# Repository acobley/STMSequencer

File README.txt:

Production board was :
StmPulse-V1-G49804

*Note* the design has a fault.  R2 and R5 are attached to 5V but should be attached to +5V

I added an airwire to link them on my build.

*NOTE*  the trigger output on board StmPulse-V1-G49804 was only 3.3V whihc is not enough to trigger some modules.

*StmPulse-V2-InProgress.sch*
This fixes the above faults, it connects R2 and R5 to +5V and adds output transistors on the gates to give 5V.

StmPulse-V2-InProgress has *NOT* been built or tested.

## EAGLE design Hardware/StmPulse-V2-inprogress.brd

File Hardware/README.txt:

Production board was :
StmPulse-V1-G49804

*Note* the design has a fault.  R2 and R5 are attached to 5V but should be attached to +5V

I added an airwire to link them on my build.

*NOTE*  the trigger output on board StmPulse-V1-G49804 was only 3.3V whihc is not enough to trigger some modules.

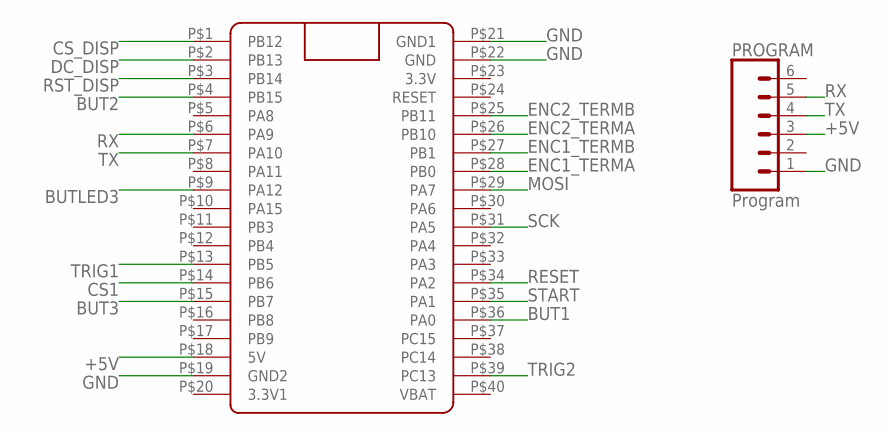
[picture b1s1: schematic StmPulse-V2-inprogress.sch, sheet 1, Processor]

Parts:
PROGRAM: Program; 1X06
U$1: Blue Pill; BLUE_PILL

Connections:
+5V: PROGRAM.3, U$1.P$18 (5V); also elsewhere on the board
BUT1: U$1.P$36 (PA0); also elsewhere on the board
BUT2: U$1.P$4 (PB15); also elsewhere on the board
BUT3: U$1.P$15 (PB7); also elsewhere on the board
BUTLED3: U$1.P$9 (PA12); also elsewhere on the board
CS1: U$1.P$14 (PB6); also elsewhere on the board
CS_DISP: U$1.P$1 (PB12); also elsewhere on the board
DC_DISP: U$1.P$2 (PB13); also elsewhere on the board
ENC1_TERMA: U$1.P$28 (PB0); also elsewhere on the board
ENC1_TERMB: U$1.P$27 (PB1); also elsewhere on the board
ENC2_TERMA: U$1.P$26 (PB10); also elsewhere on the board
ENC2_TERMB: U$1.P$25 (PB11); also elsewhere on the board
GND: PROGRAM.1, U$1.P$19 (GND2), U$1.P$21 (GND1), U$1.P$22 (GND); also elsewhere on the board
MOSI: U$1.P$29 (PA7); also elsewhere on the board
RESET: U$1.P$34 (PA2); also elsewhere on the board
RST_DISP: U$1.P$3 (PB14); also elsewhere on the board
RX: PROGRAM.5, U$1.P$6 (PA9)
SCK: U$1.P$31 (PA5); also elsewhere on the board
START: U$1.P$35 (PA1); also elsewhere on the board
TRIG1: U$1.P$13 (PB5); also elsewhere on the board
TRIG2: U$1.P$39 (PC13); also elsewhere on the board
TX: PROGRAM.4, U$1.P$7 (PA10)

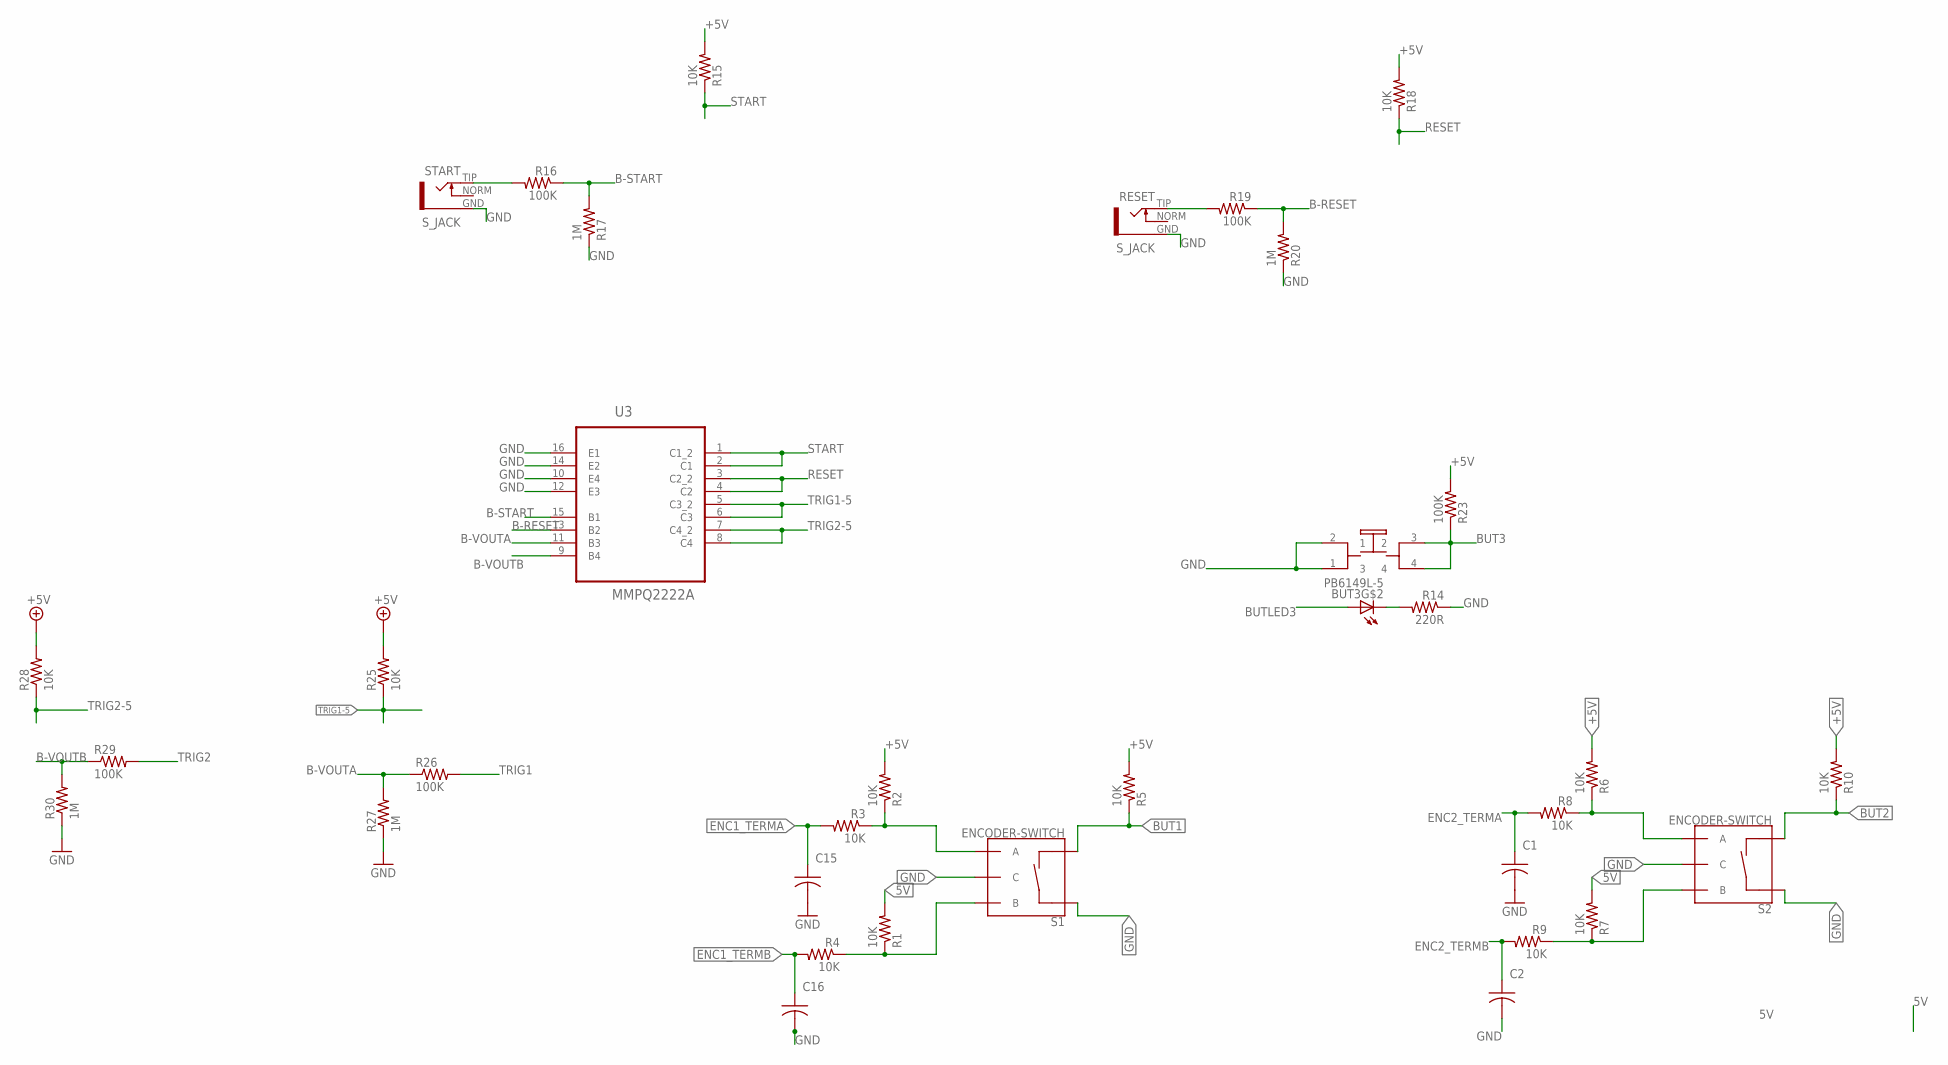
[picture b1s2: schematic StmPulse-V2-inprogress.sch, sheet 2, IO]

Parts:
BUT3: PB6149L-5; PB6149L
C1, C2, C15, C16: 10nF; C0805
R1, R2, R3, R4, R5, R6, R7, R8, R9, R10, R15, R18, R25, R28: 10K; R0805
R14: 220R; R0805
R16, R19, R23, R26, R29: 100K; R0805
R17, R20, R27, R30: 1M; R0805
RESET: S_JACK
S1, S2: ENCODER-SWITCH; ROTARY_ENC_PLAIN
START: S_JACK
U3: MMPQ2222A; SOIC127P600X175-16N

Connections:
5V: R1.2, R7.2
+5V: R2.2, R5.2, R6.2, R10.2, R15.2, R18.2, R23.2, R25.2, R28.2; also elsewhere on the board
B-RESET: R19.1, R20.2, U3.13 (B2)
B-START: R16.1, R17.2, U3.15 (B1)
B-VOUTA: R26.1, R27.2, U3.11 (B3)
B-VOUTB: R29.1, R30.2, U3.9 (B4)
BUT1: R5.1, S1.SW-; also elsewhere on the board
BUT2: R10.1, S2.SW-; also elsewhere on the board
BUT3: BUT3.3 (2), BUT3.4, R23.1; also elsewhere on the board
BUTLED3: BUT3.A; also elsewhere on the board
ENC1_TERMA: C15.1, R3.2; also elsewhere on the board
ENC1_TERMB: C16.1, R4.2; also elsewhere on the board
ENC2_TERMA: C1.1, R8.2; also elsewhere on the board
ENC2_TERMB: C2.1, R9.2; also elsewhere on the board
GND: BUT3.1 (3), BUT3.2 (1), C1.2, C2.2, C15.2, C16.2, R14.1, R17.1, R20.1, R27.1, R30.1, RESET.GND, S1.C, S1.SW+, S2.C, S2.SW+, START.GND, U3.10 (E4), U3.12 (E3), U3.14 (E2), U3.16 (E1); also elsewhere on the board
unnamed: R6.1, R8.1, S2.A
unnamed: R7.1, R9.1, S2.B
unnamed: R2.1, R3.1, S1.A
unnamed: R1.1, R4.1, S1.B
unnamed: BUT3.K (C), R14.2
unnamed: R19.2, RESET.TIP
unnamed: R16.2, START.TIP
RESET: R18.1, U3.3 (C2_2), U3.4 (C2); also elsewhere on the board
START: R15.1, U3.1 (C1_2), U3.2 (C1); also elsewhere on the board
TRIG1: R26.2; also elsewhere on the board
TRIG1-5: R25.1, U3.5 (C3_2), U3.6 (C3); also elsewhere on the board
TRIG2: R29.2; also elsewhere on the board
TRIG2-5: R28.1, U3.7 (C4_2), U3.8 (C4); also elsewhere on the board

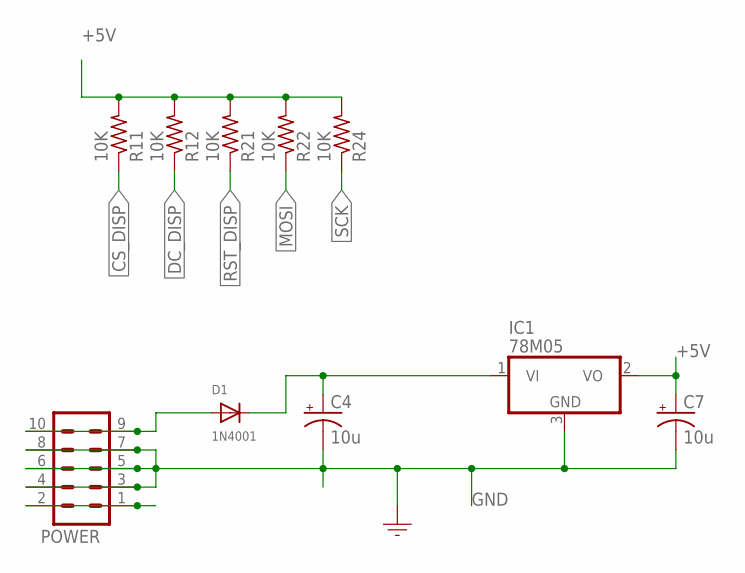
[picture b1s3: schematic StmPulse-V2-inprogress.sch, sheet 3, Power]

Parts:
C4, C7: 10u; 153CLV-0505
D1: 1N4001; SMADIODE
IC1: 78M05; TO252
POWER: CONN_05X2SHD_SMD; 2X5-SHROUDED_SMD
R11, R12, R21, R22, R24: 10K; R0805

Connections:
+5V: C7.+, IC1.2 (VO), R11.2, R12.2, R21.2, R22.2, R24.2; also elsewhere on the board
+12V: C4.+, D1.C, IC1.1 (VI)
CS_DISP: R11.1; also elsewhere on the board
DC_DISP: R12.1; also elsewhere on the board
GND: C4.-, C7.-, IC1.3 (GND), POWER.3, POWER.4, POWER.5, POWER.6, POWER.7, POWER.8; also elsewhere on the board
MOSI: R22.1; also elsewhere on the board
unnamed: D1.A, POWER.9, POWER.10
unnamed: POWER.1, POWER.2
RST_DISP: R21.1; also elsewhere on the board
SCK: R24.1; also elsewhere on the board

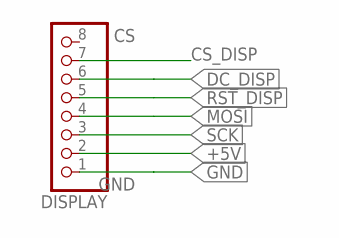
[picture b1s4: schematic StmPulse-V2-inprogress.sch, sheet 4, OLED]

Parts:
DISPLAY: MICROBUILDER_HEADER-1X8ROUND; MICROBUILDER_1X08_ROUND

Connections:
+5V: DISPLAY.2; also elsewhere on the board
CS_DISP: DISPLAY.7; also elsewhere on the board
DC_DISP: DISPLAY.6; also elsewhere on the board
GND: DISPLAY.1; also elsewhere on the board
MOSI: DISPLAY.4; also elsewhere on the board
RST_DISP: DISPLAY.5; also elsewhere on the board
SCK: DISPLAY.3; also elsewhere on the board

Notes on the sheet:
GND

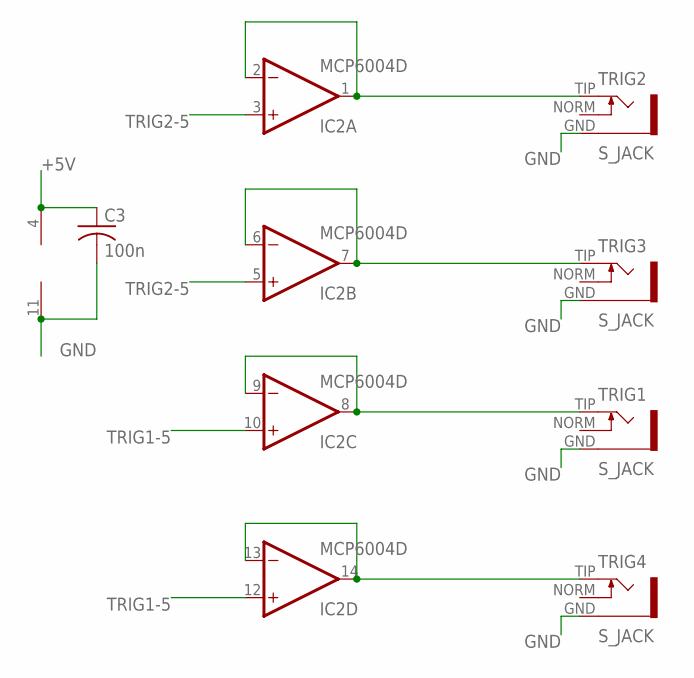
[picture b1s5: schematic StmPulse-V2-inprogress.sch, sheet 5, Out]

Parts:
C3: 100n; C0805K
IC2: MCP6004D; SO14
TRIG1, TRIG2, TRIG3, TRIG4: S_JACK

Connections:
+5V: C3.1, IC2.4 (V+); also elsewhere on the board
GND: C3.2, IC2.11 (V-), TRIG1.GND, TRIG2.GND, TRIG3.GND, TRIG4.GND; also elsewhere on the board
unnamed: IC2.1 (OUT), IC2.2 (-IN), TRIG2.TIP
unnamed: IC2.8 (OUT), IC2.9 (-IN), TRIG1.TIP
unnamed: IC2.6 (-IN), IC2.7 (OUT), TRIG3.TIP
unnamed: IC2.13 (-IN), IC2.14 (OUT), TRIG4.TIP
TRIG1-5: IC2.10 (+IN), IC2.12 (+IN); also elsewhere on the board
TRIG2-5: IC2.3 (+IN), IC2.5 (+IN); also elsewhere on the board

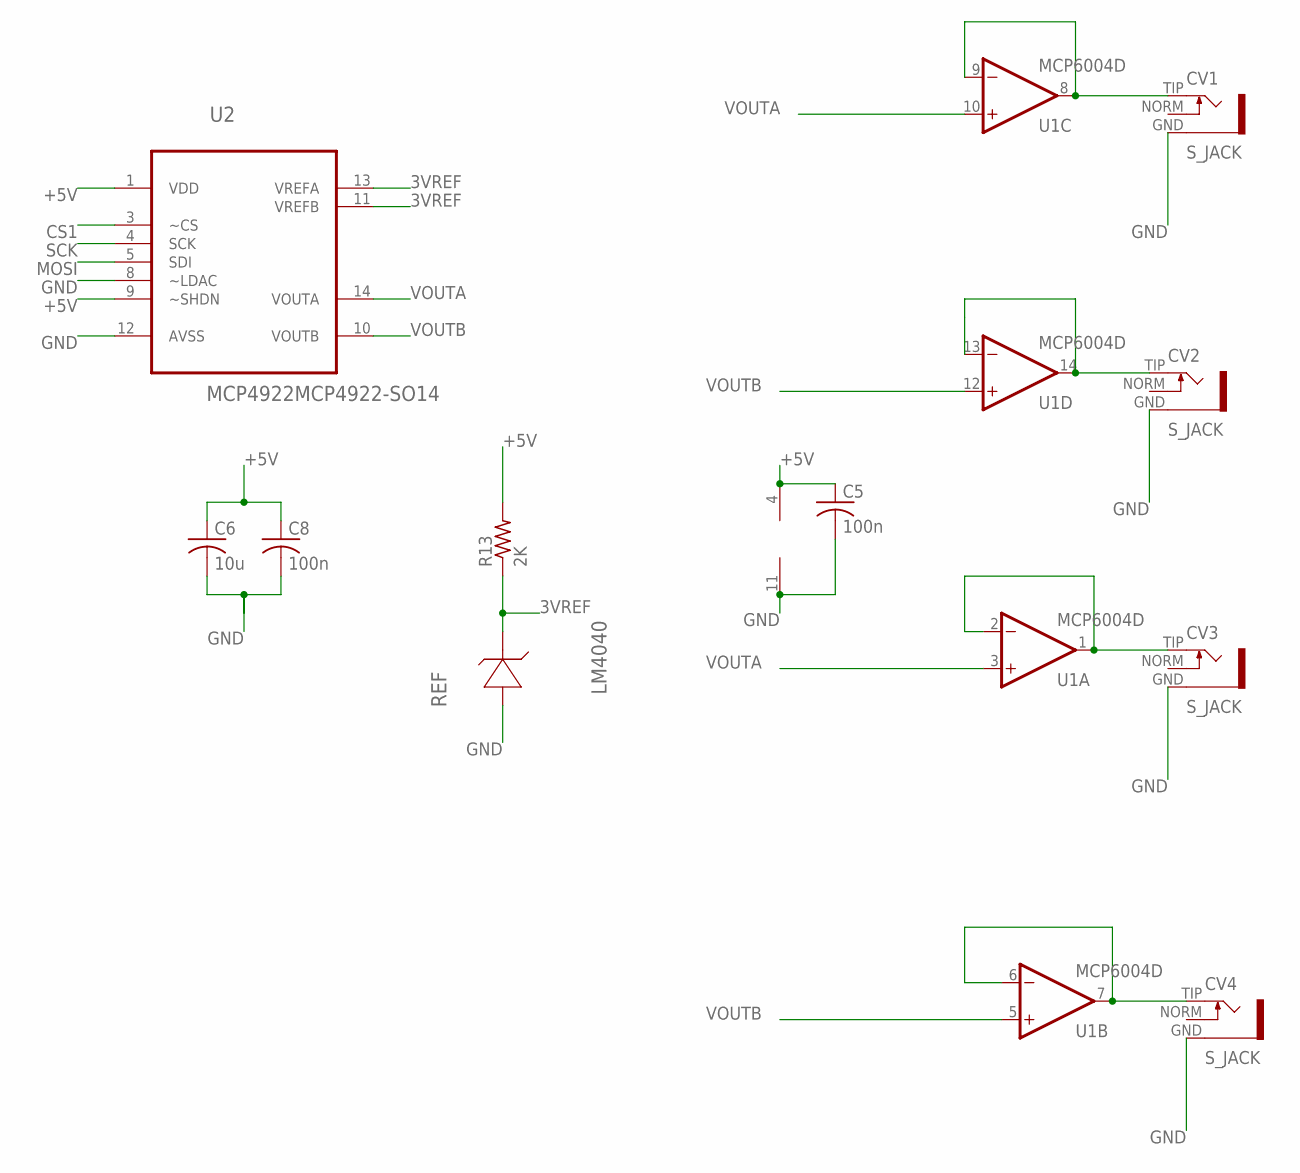
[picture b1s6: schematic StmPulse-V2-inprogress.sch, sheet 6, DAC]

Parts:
C5, C8: 100n; C0805K
C6: 10u; C0805K
CV1, CV2, CV3, CV4: S_JACK
R13: 2K; R0805
REF: LM4040; SOT95P237X112-3N; MPN LM4040A30IDBZT
U1: MCP6004D; SO14
U2: MCP4922MCP4922-SO14; SO14

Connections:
3VREF: R13.1, REF.1 (CATHODE), U2.11 (VREFB), U2.13 (VREFA)
+5V: C5.1, C6.1, C8.1, R13.2, U1.4 (V+), U2.1 (VDD), U2.9 (~SHDN); also elsewhere on the board
CS1: U2.3 (~CS); also elsewhere on the board
GND: C5.2, C6.2, C8.2, CV1.GND, CV2.GND, CV3.GND, CV4.GND, REF.2 (ANODE), U1.11 (V-), U2.8 (~LDAC), U2.12 (AVSS); also elsewhere on the board
MOSI: U2.5 (SDI); also elsewhere on the board
unnamed: CV3.TIP, U1.1 (OUT), U1.2 (-IN)
unnamed: CV4.TIP, U1.6 (-IN), U1.7 (OUT)
unnamed: CV1.TIP, U1.8 (OUT), U1.9 (-IN)
unnamed: CV2.TIP, U1.13 (-IN), U1.14 (OUT)
SCK: U2.4 (SCK); also elsewhere on the board
VOUTA: U1.3 (+IN), U1.10 (+IN), U2.14 (VOUTA)
VOUTB: U1.5 (+IN), U1.12 (+IN), U2.10 (VOUTB)

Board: 2 copper layers, 68 parts (14 on the bottom side), 50 nets, no tracks yet.

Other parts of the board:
U$2, U$3, U$4, U$5: MOUNTING_HOLE

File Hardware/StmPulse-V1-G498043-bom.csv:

"Library","Qty","Parts","Description","Value","Package","LABEL","LABLEL","MPN","OC_FARNELL","OC_NEWARK","PACKAGE","PROD_ID","RS-PART","SF_SKU","SUPPLIER",
"INSTRUO","1","T1_CLOCK","","2N3904","TRANSISTOR_SINGLE_N-TYPE","","T1_Start","","","","","","725-8616 ","","",
"BluePill","1","U$1","","Blue Pill","BLUE_PILL","","","","","","","","","","",
"GMSN-R2Project","1","U2-MCP4922","","MCP4922MCP4922-SO14","SO14","","","","","","","","402-910 ","","",
"INSTRUO","1","BUT3","","PB6149L-5","PB6149L","","","","","","","","","","",
"INSTRUO","10","CV1, CV2, CV3, CV4, RESET, START, TRIG1, TRIG2, TRIG3, TRIG4","","S_JACK","S_JACK","","","","","","","","","","",
"INSTRUO","1","T2_RESET","","TRANSISTOR_MMBT3904","TRANSISTOR_SINGLE_N-TYPE","T2_Reset","","","","","","","725-8616 ","","",
"rcl","3","C3, C5, C8","CAPACITOR, American symbol","100n","C0805K","","","","","","","","","","",
"rcl","4","C1, C2, C15, C16","CAPACITOR, American symbol","10nF","C0805","","","","","","","","","","",
"rcl","1","C6","CAPACITOR, American symbol","10u","C0805K","","","","","","","","","","",
"GMSN","1","D1","Diode","1N4001","SMADIODE","","","","","","","","","","",
"SparkFun-Connectors","1","POWER","Multi connection point. Often used as Generic Header-pin footprint for 0.1 inch spaced/style header connections","","2X5-SHROUDED_SMD","","","","","","","CONN-09508","","","",
"SparkFun-Connectors","1","PROGRAM","Multi connection point. Often used as Generic Header-pin footprint for 0.1 inch spaced/style header connections","Program","1X06","","","","","","","CONN-08437","","","",
"GMSN-R2Project","1","IC2","OP AMP","MCP6004D","SO14","","","","","","","","","","",
"GMSN-R2Project","1","U1","OP AMP","MCP6004D","SO14","","","","","","","","628-3481 (10)","","",
"Adafruit_1.3_128x64_OLED","1","DISPLAY","PIN HEADER","","MICROBUILDER_1X08_ROUND","","","","","","","","","","",
"GMSN","2","C4, C7","POLARIZED CAPACITOR, American symbol","10u","153CLV-0505","","","","","","","","","","",
"GMSN-R2Project","1","REF","PRECISION MICROPOWER SHUNT VOLTAGE REFERENCE","LM4040","SOT95P237X112-3N","","","LM4040A30IDBZT","1755108","58K5870","3-SOT-23","","809-6343","","TEXAS INSTRUMENTS",
"GMSN","1","IC1","Positive VOLTAGE REGULATOR","78M05","TO252","","","","","","","","","","",
"rcl","3","R16, R19, R23","RESISTOR, American symbol","100K","R0805","","","","","","","","","","",
"rcl","17","R1, R2, R3, R4, R5, R6, R7, R8, R9, R10, R11, R12, R15, R18, R21, R22, R24","RESISTOR, American symbol","10K","R0805","","","","","","","","","","",
"rcl","2","R17, R20","RESISTOR, American symbol","1M","R0805","","","","","","","","","","",
"rcl","1","R14","RESISTOR, American symbol","220R","R0805","","","","","","","","","","",
"rcl","1","R13","RESISTOR, American symbol","2K","R0805","","","","","","","","","","",
"SparkFun-Switches","2","S1, S2","Rotary Encoder w/ Select Switch","ENCODER-SWITCH","ROTARY_ENC_PLAIN","","","","","","","","","COM-09117","",

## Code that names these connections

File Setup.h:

#include "SPI.h"
#include "fonts.h"


//Encoder
#define encA PB0
#define encB PB1

#define enc2A PB10 //11
#define enc2B PB11 //10
#define BUT1 PA0
#define BUT2 PB15
#define STARTBUT PB7
#define BUTLED3 PA12
#define START PA2
#define RESET PA1

int DAC = PB6; //????
int Gate1 = PB5;
int Gate2 = PC13;
byte CV1 = 1;
byte CV2 = 0;
char Modes[] = {'P', 'L', 'N', 'O', 'M'};
char Modes2[] = {'P', 'S'};
byte Mode = 0;
byte Mode2 = 0;

int encAVal, encALast, encBVal;
int encAVal2, encALast2, encBVal2;

HardwareTimer MainTimer(1);

long ClockF = 72000000;
struct ClockStruct {
  char Name[15];
  long Psc = 0;
  long Arr = 0;
};

struct PWMStruct{
 long PWM1=1;
 long PWM2=1;
 long PWM1Counter=0;
 long PWM2Counter=0;
 boolean Phase=0;
};

ClockStruct MainClock;
PWMStruct BeatPWMS;

PWMStruct SequencePWMS;
ClockStruct SequenceClock;


const short MaxPatternLength = 16;
short Timers[MaxPatternLength] ;
short calcBeatPos[MaxPatternLength];
short BeatPos[MaxPatternLength] ;
short Notes[MaxPatternLength] ;
short Octave[MaxPatternLength] ;
short Volume[MaxPatternLength] ;
int countlength = sizeof(Notes) / sizeof(short);

const short NoteLengths[6] = {0, 1, 2, 4, 8, 16};
const float BeatLengths[6] = {0, 4, 2, 1, 0.5, 0.25};
const short NumPatterns = 7;





const int DefaultTempo=120;
int Tempo = DefaultTempo;
long BaseTime = 1000000L * (4 * 60) / Tempo;
long BeatTime = 1000000L * 60 / Tempo;
short GateLength = 4;
long SeqGateTime = BaseTime * (GateLength / 8);
long ms15 = 015000L;
const short MinTempo = 30;
const short MaxTempo = 300;

int PlaceCount = 0;
int ErasePos = -1;
int bErasePos;
int Beat = 1;
int MaxBeat = 10;

float NumberOfBeats = 1.0;
short CurrentPattern = 0;
short NextPattern = -1;




short encPos = Tempo;
short NewEncPos = Tempo;
short encPos2 = GateLength;
short NewEncPos2 = GateLength;




//float Range = 819.2; // (2^12/5)
float Range = 1365.33333; // (2^12/3)

volatile int hKey ;
volatile int hOctave;
volatile int hNote;
volatile int houtValue;

int CX = 0;
int CY = 0;
int Width = 8;
int Height = 8;


void SetupEncoders() {
  pinMode(encA, INPUT);
  pinMode(encB, INPUT);
  pinMode(enc2A, INPUT);
  pinMode(enc2B, INPUT);

  //digitalWrite(encA, HIGH);
  //digitalWrite(encB, HIGH);
  //digitalWrite(enc2A, HIGH);
  //digitalWrite(enc2B, HIGH);
}


void SetupOLED() {
  _Res_Max_X = SH1106_RES_X;
  _GRAM_Col_Start = SH1106_GRAM_COL_START;
  _GRAM_Col_End = SH1106_GRAM_COL_END;
  _GRAM_Page_Start = SH1106_GRAM_PAGE_START;
  _GRAM_Page_End = SH1106_GRAM_PAGE_END;
  _RAM_Pages = SH1106_GRAM_PAGE_END - SH1106_GRAM_PAGE_START + 1;

  SPI.begin();

  SPI.setBitOrder(MSBFIRST);
  pinMode(CS_DI, OUTPUT);
  pinMode(DC_DI, OUTPUT);
  pinMode(RST_DI, OUTPUT);

  Reset();
  Cursor(0, 0);
  DrawMode(NORMAL);
  _FontType = Terminal_8pt;
  _FontHight = Terminal_8ptFontInfo.CharacterHeight;
  _FontDescriptor = Terminal_8ptFontInfo.Descriptors;
  for (int x = 0; x < 128; x++) {
    for (int y = 0; y < 64; y++) {
      Plot(x, y);
    }
    Refresh();
  }

  DrawMode(CLEAR);
  for (int x = 0; x < 128; x++) {
    for (int y = 0; y < 64; y++) {
      Plot(x, y);
    }
    Refresh();
  }

  Erase(0, 0, 128, 64);
  Refresh();

}

void SetupDacs() {
  SPI.begin();
  SPI.setBitOrder(MSBFIRST);
  pinMode(DAC, OUTPUT);

  digitalWrite(DAC, HIGH);

}



void SetupGates() {
  pinMode(Gate2, OUTPUT);
  pinMode(Gate1, OUTPUT);
}

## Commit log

2019-05-27 Added underline
2019-05-28 updated underline
2019-05-28 updated Timer to use HardwareTimer timer(1);
2019-05-28 updated Timer to refresh
2019-05-30 added totary tempo encode
2019-05-31 added V out
2019-06-02 started Note font
2019-06-02 Note font
2019-06-07 added switch interupt
2019-06-11 added encider2
2019-06-11 added encoder2
2019-06-15 moved lines on display up
2019-06-17 Added Hardware
2019-06-18 moved mounting holes
2019-06-22 Changed C and R to 805
2019-08-11 Updated encoder switches
2019-08-11 updated hardware
2020-01-13 V1 Board Ordered
2020-01-13 gerfiles for V1
2020-05-02 Added BOM
2020-05-03 updated BOM and RS component
2020-05-10 Changed calibration to 3V
2020-05-10 Changed gates pins and added CV variable.
2020-05-11 fixedCV order
2020-05-15 added mode2 for sequence selection
2020-05-16 added sequence select code
2020-05-17 Added Save to EEPROM
2020-07-19 added note about fault with R2 and R5
2020-07-19 Added note about trigger voltage
2020-07-19 added StmPulse-V2-InProgress.sch and brd files
2020-07-19 fixed timing issues
2020-08-30 added Whole and HAlf notes
2020-08-30 added whole note pattern
2020-10-25 Pushing old code for the record, does not compile
2020-11-12 Splitting up files
2020-11-12 added V2 hardware, fixing wiring fault
2020-11-15 added .h files
2020-11-15 Fixed thempo jump on pattern change
2020-11-19 fixed hole and half notes
2020-11-19 fixed stuck notes
2021-02-01 moved towards master clock

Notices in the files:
Hardware/StmPulse-V2-inprogress.brd:
CC BY 3.0
parts and their libraries:
SparkFun-Switches: Licensing: Creative Commons ShareAlike 4.0 International - https://creativecommons.org/licenses/by-sa/4.0
